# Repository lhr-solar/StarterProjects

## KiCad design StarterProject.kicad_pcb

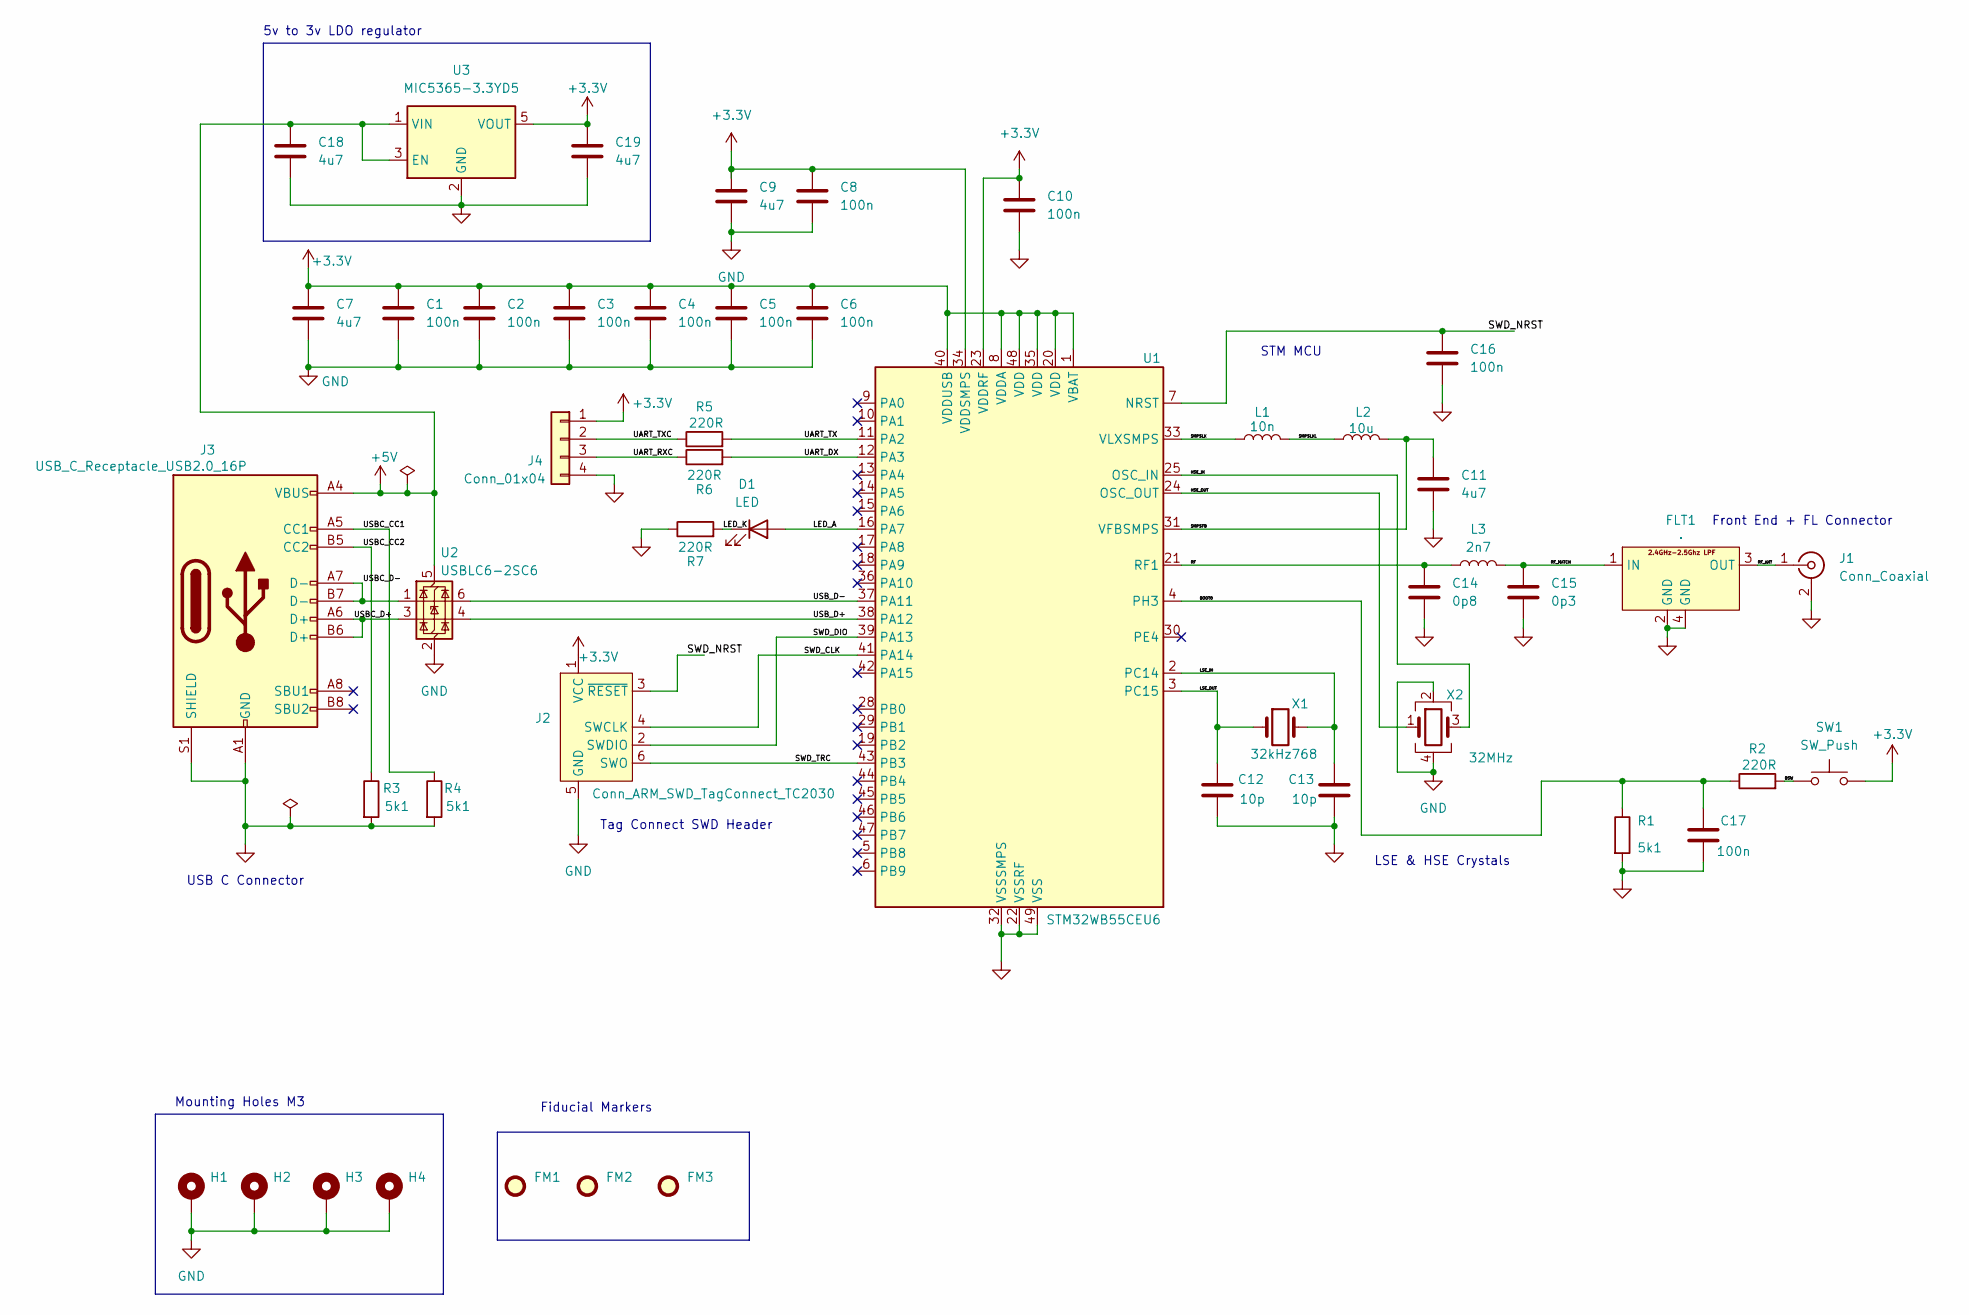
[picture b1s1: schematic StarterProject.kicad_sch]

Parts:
C1, C2, C3, C4, C5, C6, C8, C10, C16, C17: 100n; C_0402_1005Metric
C7, C9, C11, C18, C19: 4u7; C_0603_1608Metric
C12, C13: 10p; C_0402_1005Metric
C14: 0p8; C_0402_1005Metric
C15: 0p3; C_0402_1005Metric
D1: LED; LED_0402_1005Metric; Part # 150040RS73240
FLT1: DLF162500LT-5028A1; Untitled; Part # DLF162500LT-5028A1
FM1, FM2, FM3: Fiducial; Fiducial_1mm_Mask2mm
H1, H2, H3, H4: MountingHole_Pad; MountingHole_2.2mm_M2_Pad_Via
J1: Conn_Coaxial; U.FL_Hirose_U.FL-R-SMT-1_Vertical
J2: Conn_ARM_SWD_TagConnect_TC2030; Tag-Connect_TC2030-IDC-FP_2x03_P1.27mm_Vertical
J3: USB_C_Receptacle_USB2.0_16P; USB_C_Receptacle_GCT_USB4105-xx-A_16P_TopMnt_Horizontal; Part # USB4105-GF-A
J4: Conn_01x04; Molex_PicoBlade_53048-0410_1x04_P1.25mm_Horizontal; Part # 53048-0410
L1: 10n; L_0402_1005Metric; Part # LQG15HN10NJ02D
L2: 10u; L_0805_2012Metric; Part # LQM21FN100M70L
L3: 2n7; L_0402_1005Metric; Part # LQG15HS2N7S02D
R1, R3, R4: 5k1; R_0402_1005Metric; Part # RC0402FR-075K1L
R2, R5, R6, R7: 220R; R_0402_1005Metric; Part # RC0402FR-0722RL
SW1: SW_Push; SW_SPST_CK_RS282G05A3; Part # RS-282G05A3-SM RT
U1: STM32WB55CEU6; QFN-48-1EP_7x7mm_P0.5mm_EP5.6x5.6mm; Part # STM32WB55CEU6
U2: USBLC6-2SC6; SOT-23-6; Part # USBLC6-2SC6
U3: MIC5365-3.3YD5; TSOT-23-5; Part # MIC5365-3.3YD5-TR
X1: 32kHz768; Crystal_SMD_2012-2Pin_2.0x1.2mm; Part # NX2012SA-32.768K-STD-MUB-1
X2: 32MHz; Crystal_SMD_2016-4Pin_2.0x1.6mm; Part # NX2016SA-32M-EXS00A-CS06465

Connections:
+3.3V: C1.1, C2.1, C3.1, C4.1, C5.1, C6.1, C7.1, C8.1, C9.1, C10.1, C19.1, J2.1 (VCC), J4.1, SW1.2, U1.1 (VBAT), U1.8 (VDDA), U1.20 (VDD), U1.23 (VDDRF), U1.34 (VDDSMPS), U1.35 (VDD), U1.40 (VDDUSB), U1.48 (VDD), U3.5 (VOUT)
+5V: C18.1, J3.A4 (VBUS), J3.A9 (VBUS), J3.B4 (VBUS), J3.B9 (VBUS), U2.5 (VBUS), U3.1 (VIN), U3.3 (EN)
/BOOT0: C17.1, R1.1, R2.1, U1.4 (PH3)
/BSW: R2.2, SW1.1
/HSE_IN: U1.25 (OSC_IN), X2.3
/HSE_OUT: U1.24 (OSC_OUT), X2.1
/LED_A: D1.2 (A), U1.16 (PA7)
/LED_K: D1.1 (K), R7.2
/LSE_IN: C13.1, U1.2 (PC14), X1.2
/LSE_OUT: C12.1, U1.3 (PC15), X1.1
/RF: C14.1, L3.1, U1.21 (RF1)
/RF_ANT: FLT1.3 (OUT), J1.1 (In)
/RF_MATCH: C15.1, FLT1.1 (IN), L3.2
/SMPSFB: C11.1, L2.2, U1.31 (VFBSMPS)
/SMPSLX: L1.1, U1.33 (VLXSMPS)
/SMPSLXL: L1.2, L2.1
/SWD_CLK: J2.4 (SWCLK), U1.41 (PA14)
/SWD_DIO: J2.2 (SWDIO), U1.39 (PA13)
/SWD_NRST: C16.1, J2.3 (~RESET), U1.7 (NRST)
/SWD_TRC: J2.6 (SWO), U1.43 (PB3)
/UART_DX: R6.2, U1.12 (PA3)
/UART_RXC: J4.3, R6.1
/UART_TX: R5.2, U1.11 (PA2)
/UART_TXC: J4.2, R5.1
/USBC_CC1: J3.A5 (CC1), R4.1
/USBC_CC2: J3.B5 (CC2), R3.1
/USBC_D+: J3.A6 (D+), J3.B6 (D+), U2.3 (I/O2)
/USBC_D-: J3.A7 (D-), J3.B7 (D-), U2.1 (I/O1)
/USB_D+: U1.38 (PA12), U2.4 (I/O2)
/USB_D-: U1.37 (PA11), U2.6 (I/O1)
GND: C1.2, C2.2, C3.2, C4.2, C5.2, C6.2, C7.2, C8.2, C9.2, C10.2, C11.2, C12.2, C13.2, C14.2, C15.2, C16.2, C17.2, C18.2, C19.2, FLT1.2 (GND), FLT1.4 (GND), H1.1, H2.1, H3.1, H4.1, J1.2 (Ext), J2.5 (GND), J3.A1 (GND), J3.A12 (GND), J3.B1 (GND), J3.B12 (GND), J3.S1 (SHIELD), J4.4, R1.2, R3.2, R4.2, R7.1, U1.22 (VSSRF), U1.32 (VSSSMPS), U1.49 (VSS), U2.2 (GND), U3.2 (GND), X2.2, X2.4

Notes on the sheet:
STM MCU
Tag Connect SWD Header
Mounting Holes M3
Front End + FL Connector
Fiducial Markers
LSE & HSE Crystals
USB C Connector
5v to 3v LDO regulator

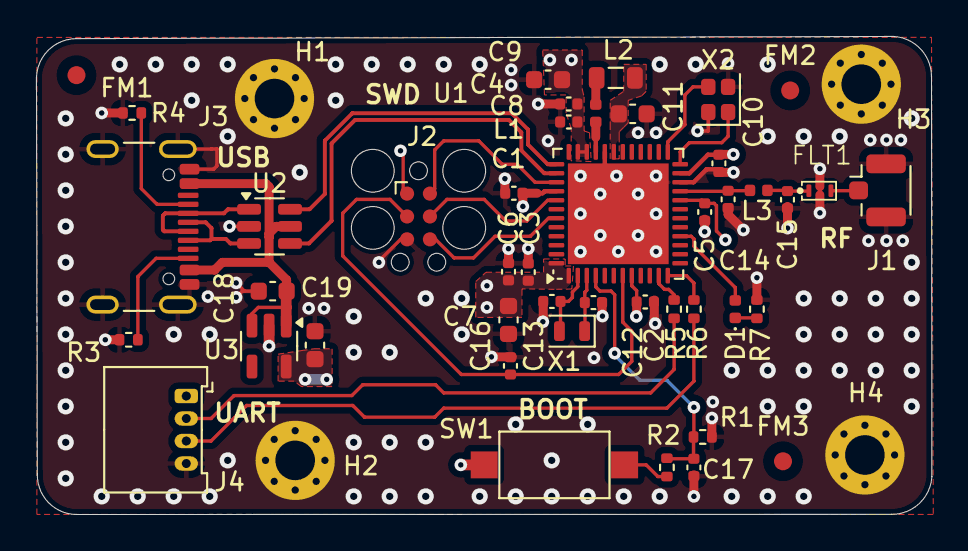
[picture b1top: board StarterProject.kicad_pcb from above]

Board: 4 copper layers, 49.7 x 26.6 mm, 48 parts (0 on the bottom side), 31 nets.

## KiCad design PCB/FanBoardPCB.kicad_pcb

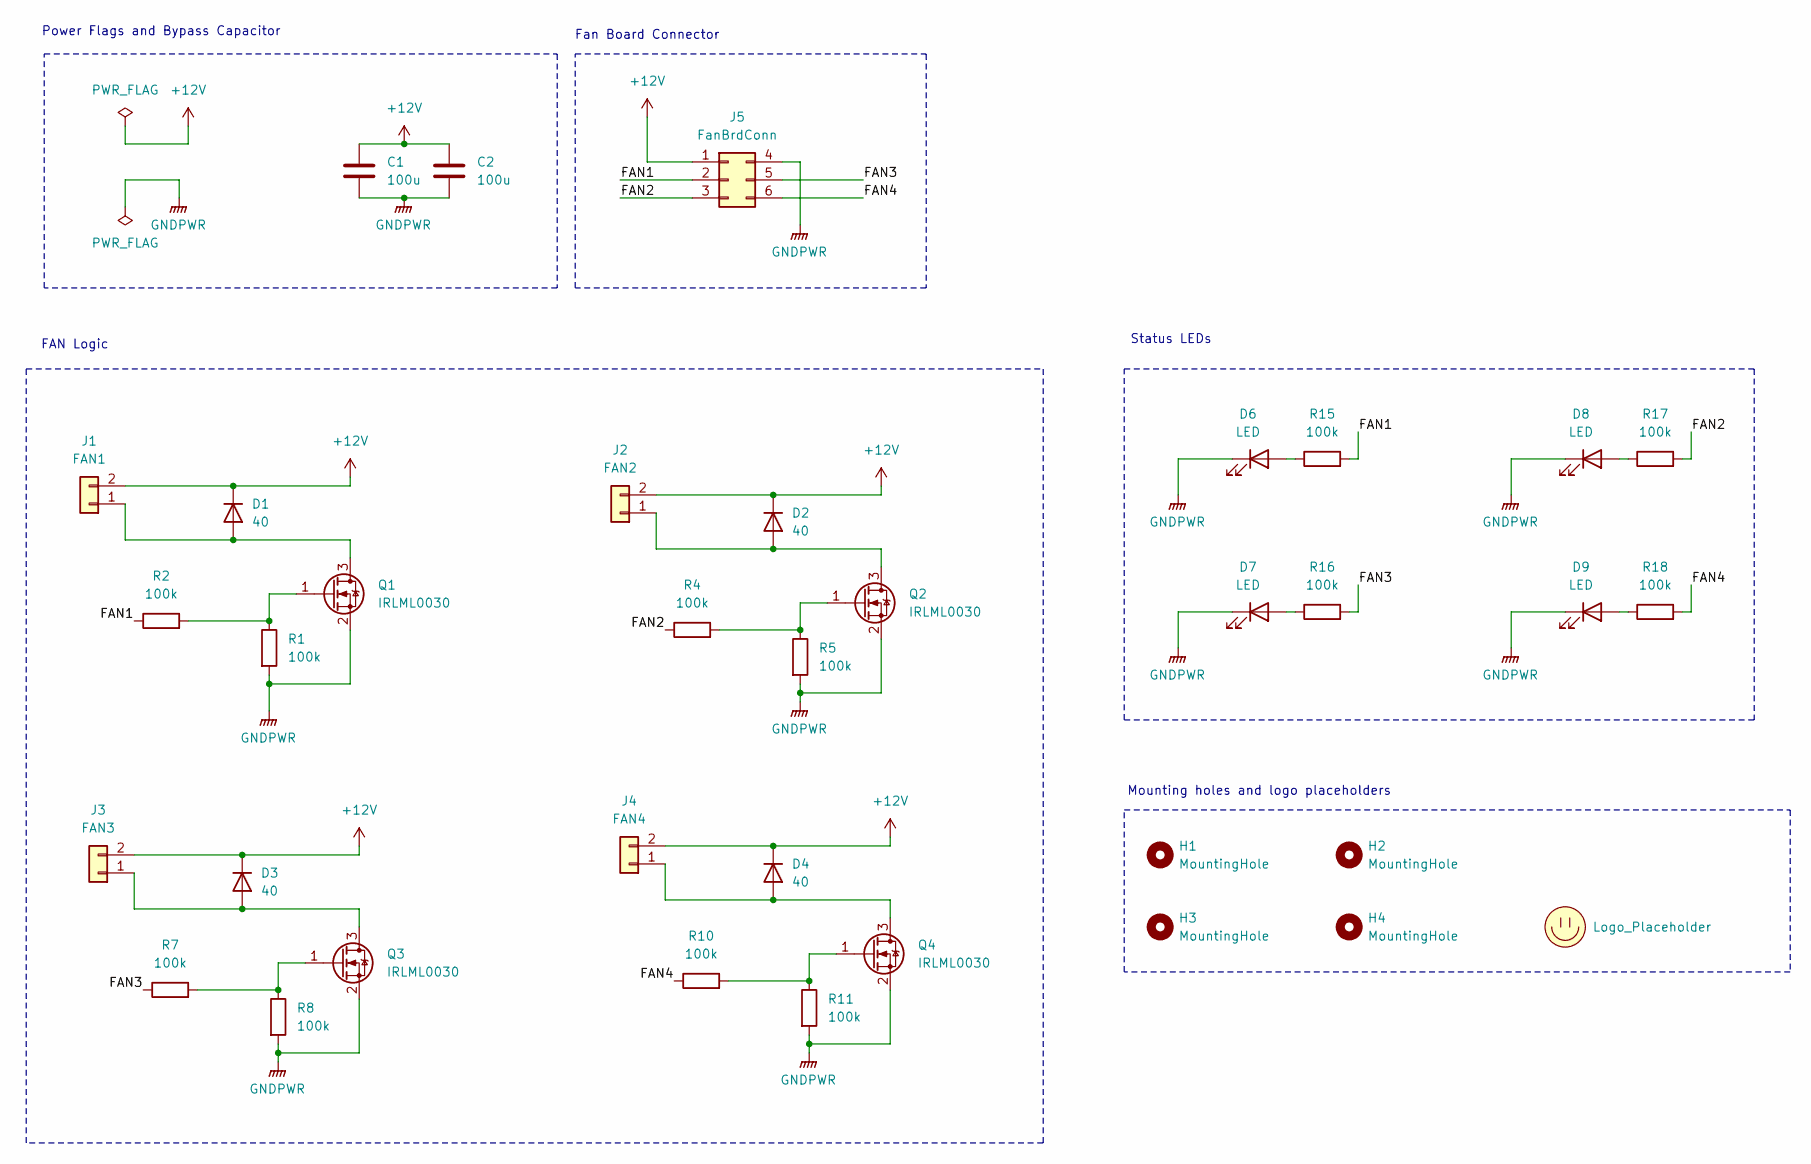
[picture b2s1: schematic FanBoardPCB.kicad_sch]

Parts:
C1, C2: 100u
D1, D2, D3, D4: 40; D_0805_2012Metric
D6, D7, D8, D9: LED; LED_0805_2012Metric
H1, H2, H3, H4: MountingHole; MountingHole_3mm
J1: FAN1; Molex_MicroFit3.0_1x2xP3.00mm_PolarizingPeg_Vertical
J2: FAN2; Molex_MicroFit3.0_1x2xP3.00mm_PolarizingPeg_Vertical
J3: FAN3; Molex_MicroFit3.0_1x2xP3.00mm_PolarizingPeg_Vertical
J4: FAN4; Molex_MicroFit3.0_1x2xP3.00mm_PolarizingPeg_Vertical
J5: FanBrdConn; Molex_Micro-Fit_3.0_43045-0612_2x03_P3.00mm_Vertical
LOGO1: Logo_Placeholder; UTSVT_Logo_Symbol
Q1, Q2, Q3, Q4: IRLML0030; SOT-23
R1, R2, R4, R5, R7, R8, R10, R11, R15, R16, R17, R18: 100k; R_0805_2012Metric

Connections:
+12V: C1.1, C2.1, D1.1 (K), D2.1 (K), D3.1 (K), D4.1 (K), J1.2, J2.2, J3.2, J4.2, J5.1
/FAN1: J5.2, R2.1, R15.2
/FAN2: J5.3, R4.1, R17.2
/FAN3: J5.5, R7.1, R16.2
/FAN4: J5.6, R10.1, R18.2
GNDPWR: C1.2, C2.2, D6.1 (K), D7.1 (K), D8.1 (K), D9.1 (K), J5.4, Q1.2 (S), Q2.2 (S), Q3.2 (S), Q4.2 (S), R1.2, R5.2, R8.2, R11.2
unnamed: D1.2 (A), J1.1, Q1.3 (D)
unnamed: D2.2 (A), J2.1, Q2.3 (D)
unnamed: D3.2 (A), J3.1, Q3.3 (D)
unnamed: D4.2 (A), J4.1, Q4.3 (D)
unnamed: D6.2 (A), R15.1
unnamed: D7.2 (A), R16.1
unnamed: D8.2 (A), R17.1
unnamed: D9.2 (A), R18.1
unnamed: Q1.1 (G), R1.1, R2.2
unnamed: Q2.1 (G), R4.2, R5.1
unnamed: Q3.1 (G), R7.2, R8.1
unnamed: Q4.1 (G), R10.2, R11.1

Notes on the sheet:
Status LEDs
FAN Logic
Power Flags and Bypass Capacitor
Fan Board Connector
Mounting holes and logo placeholders

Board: 2 copper layers, 36 parts (0 on the bottom side), 18 nets, no tracks yet.

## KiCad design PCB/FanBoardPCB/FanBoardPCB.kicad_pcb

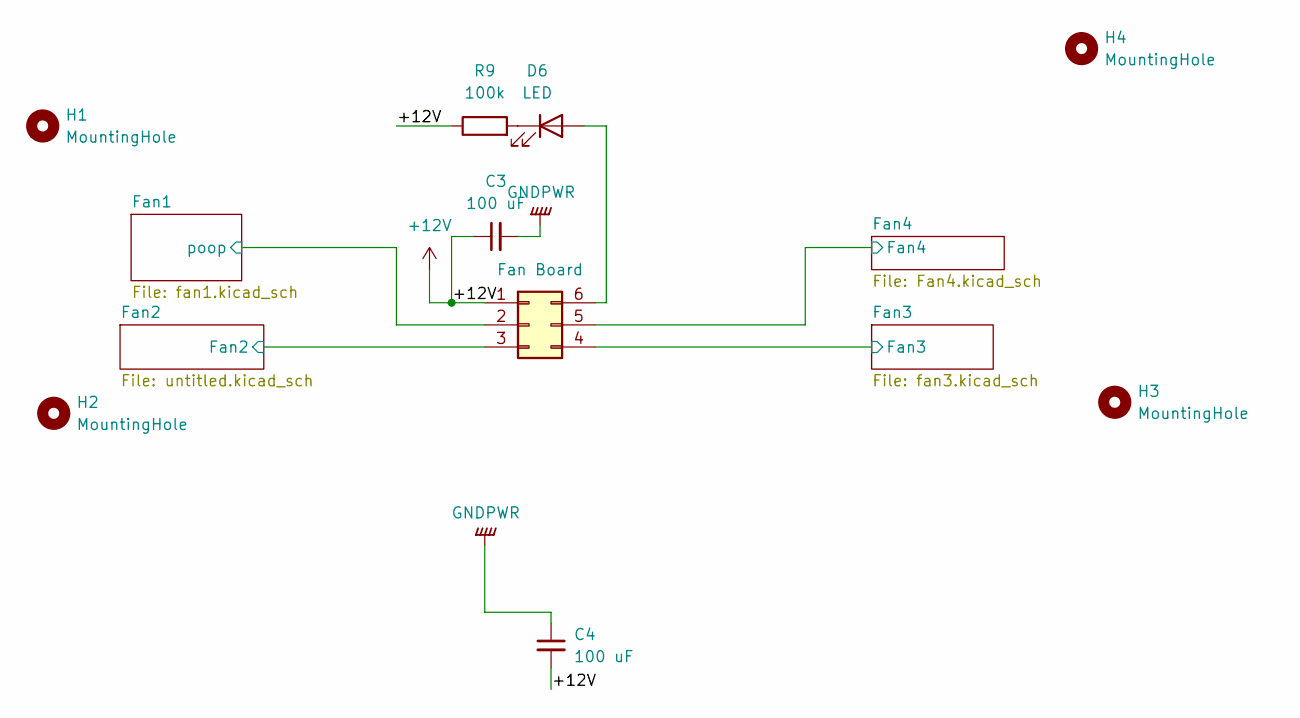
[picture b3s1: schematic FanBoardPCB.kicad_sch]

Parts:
C3, C4: 100 uF; C_0805_2012Metric
D6: LED; LED_0805_2012Metric
H1, H2, H3, H4: MountingHole; MountingHole_3mm
J5: Fan Board; Molex_Micro-Fit_3.0_43045-0612_2x03_P3.00mm_Vertical
R9: 100k; R_0805_2012Metric

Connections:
+12V: C3.1, C4.2, J5.1, R9.1; also elsewhere on the board
/Fan1/poop: J5.2; also elsewhere on the board
/Fan2/Fan2: J5.3; also elsewhere on the board
/Fan3/Fan3: J5.4; also elsewhere on the board
/Fan4/Fan4: J5.5; also elsewhere on the board
GNDPWR: C3.2, C4.1
unnamed: D6.2 (A), J5.6
unnamed: D6.1 (K), R9.2

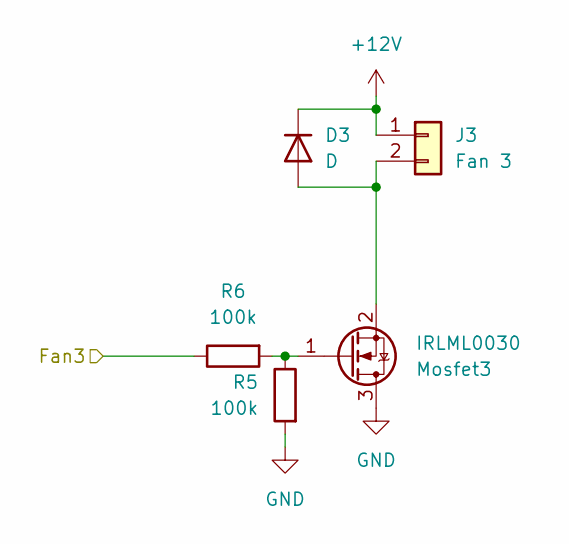
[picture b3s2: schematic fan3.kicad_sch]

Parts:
D3: D; D_0805_2012Metric
J3: Fan 3; Molex_MicroFit3.0_1x2xP3.00mm_PolarizingPeg_Vertical
Mosfet3: IRLML0030; SOT-23
R5, R6: 100k; R_0805_2012Metric

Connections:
+12V: D3.1 (K), J3.1; also elsewhere on the board
/Fan3/Fan3: R6.1; also elsewhere on the board
GND: Mosfet3.3 (D), R5.2; also elsewhere on the board
unnamed: D3.2 (A), J3.2, Mosfet3.2 (S)
unnamed: Mosfet3.1 (G), R5.1, R6.2

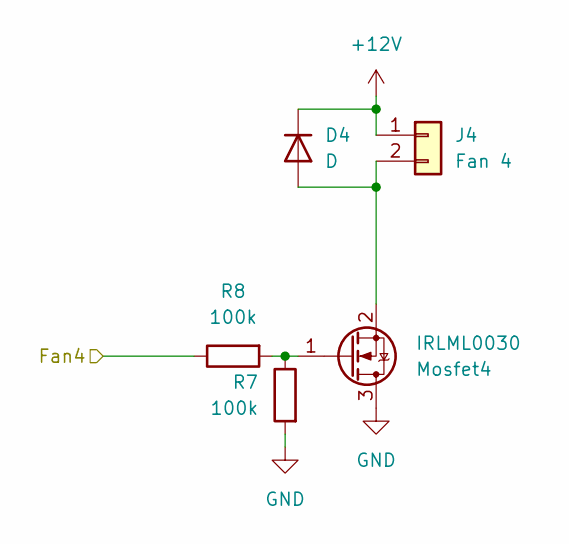
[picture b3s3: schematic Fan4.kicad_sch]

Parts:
D4: D; D_0805_2012Metric
J4: Fan 4; Molex_MicroFit3.0_1x2xP3.00mm_PolarizingPeg_Vertical
Mosfet4: IRLML0030; SOT-23
R7, R8: 100k; R_0805_2012Metric

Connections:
+12V: D4.1 (K), J4.1; also elsewhere on the board
/Fan4/Fan4: R8.1; also elsewhere on the board
GND: Mosfet4.3 (D), R7.2; also elsewhere on the board
unnamed: D4.2 (A), J4.2, Mosfet4.2 (S)
unnamed: Mosfet4.1 (G), R7.1, R8.2

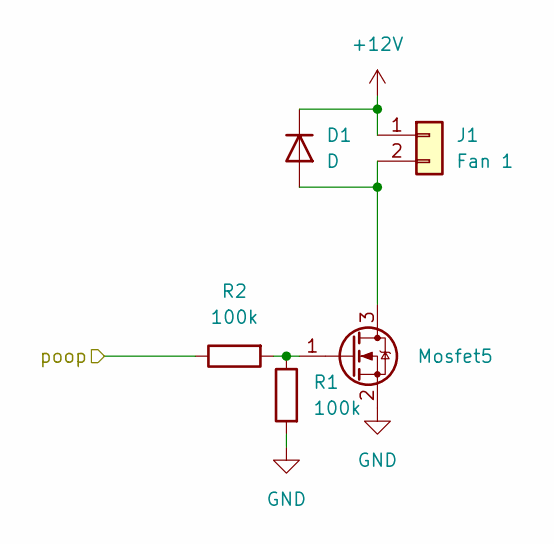
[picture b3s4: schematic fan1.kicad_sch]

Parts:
D1: D; D_0805_2012Metric
J1: Fan 1; Molex_MicroFit3.0_1x2xP3.00mm_PolarizingPeg_Vertical
Mosfet5: IRLML0030; SOT-23
R1, R2: 100k; R_0805_2012Metric

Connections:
+12V: D1.1 (K), J1.1; also elsewhere on the board
/Fan1/poop: R2.1; also elsewhere on the board
GND: Mosfet5.2 (S), R1.2; also elsewhere on the board
unnamed: D1.2 (A), J1.2, Mosfet5.3 (D)
unnamed: Mosfet5.1 (G), R1.1, R2.2

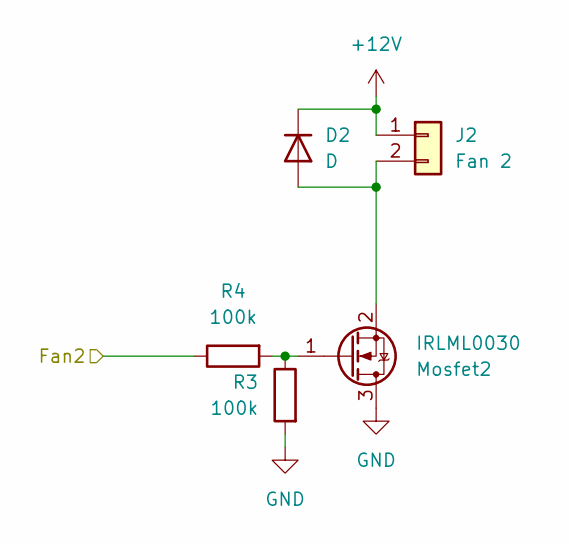
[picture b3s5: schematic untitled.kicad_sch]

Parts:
D2: D; D_0805_2012Metric
J2: Fan 2; Molex_MicroFit3.0_1x2xP3.00mm_PolarizingPeg_Vertical
Mosfet2: IRLML0030; SOT-23
R3, R4: 100k; R_0805_2012Metric

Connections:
+12V: D2.1 (K), J2.1; also elsewhere on the board
/Fan2/Fan2: R4.1; also elsewhere on the board
GND: Mosfet2.3 (D), R3.2; also elsewhere on the board
unnamed: D2.2 (A), J2.2, Mosfet2.2 (S)
unnamed: Mosfet2.1 (G), R3.1, R4.2

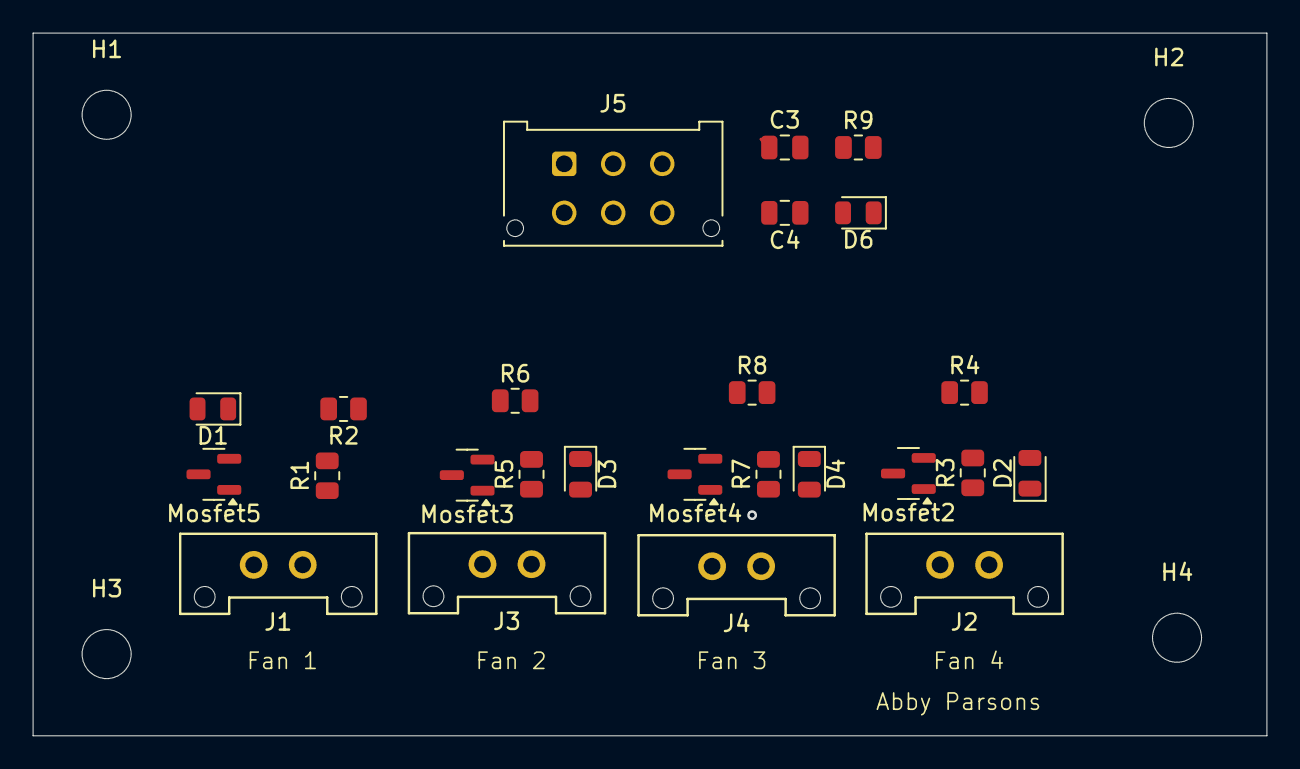
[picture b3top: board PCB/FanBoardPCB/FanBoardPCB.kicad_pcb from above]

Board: 2 copper layers, 75.5 x 43.0 mm, 29 parts (0 on the bottom side), 17 nets.

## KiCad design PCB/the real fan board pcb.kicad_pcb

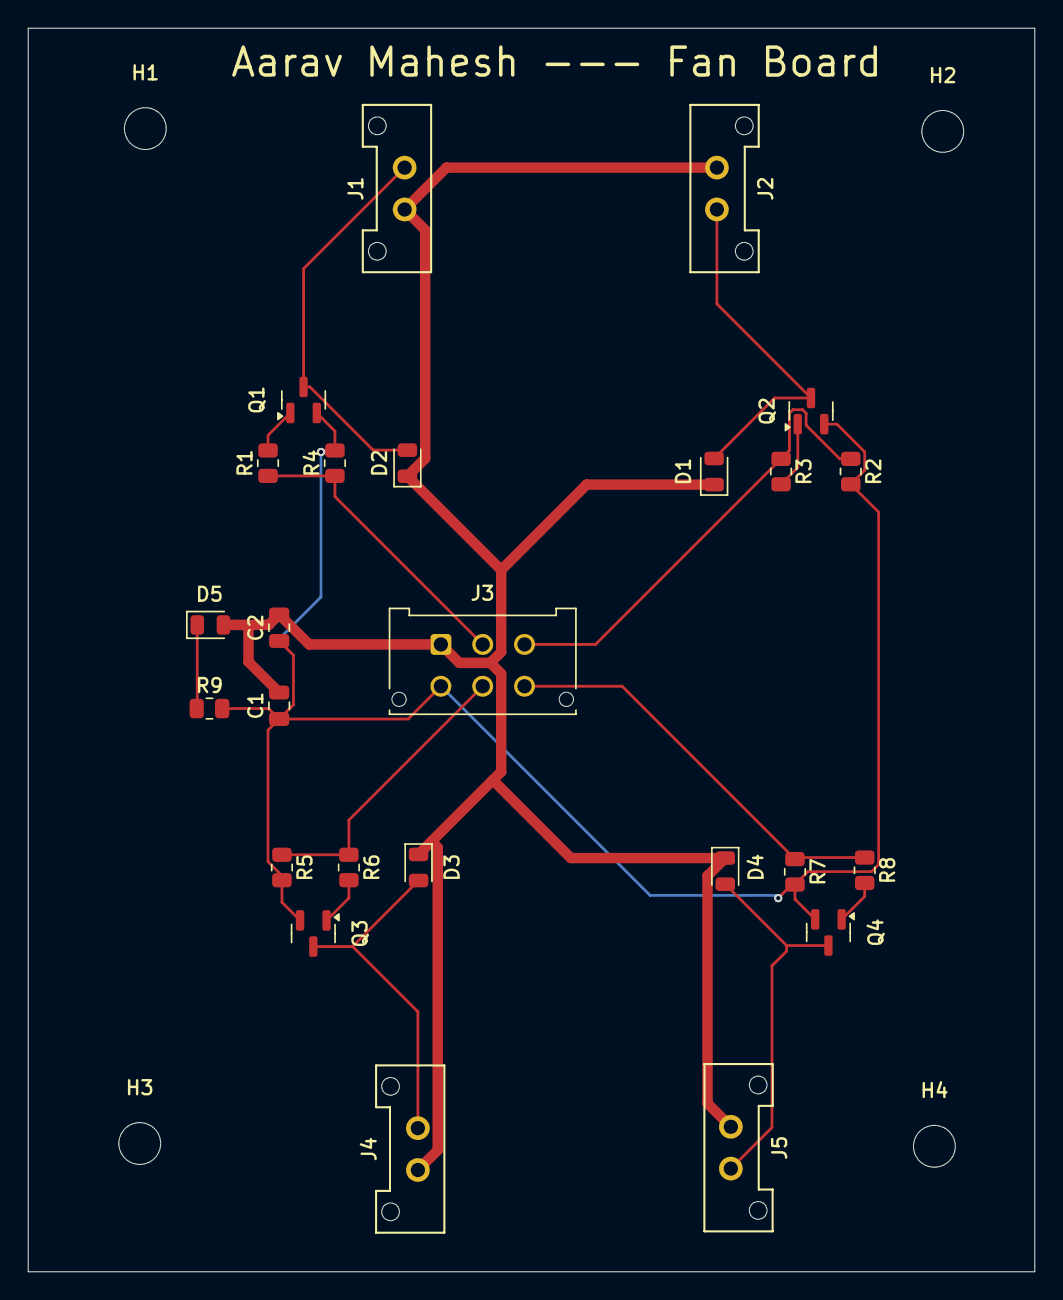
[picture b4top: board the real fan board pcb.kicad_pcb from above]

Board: 2 copper layers, 72.2 x 89.2 mm, 29 parts (0 on the bottom side), 15 nets.

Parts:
C1, C2: 100uF; C_0805_2012Metric
D1, D2, D3, D4: D; D_0805_2012Metric
D5: LED; LED_0805_2012Metric
H1, H2, H3, H4: MountingHole; MountingHole_3mm
J1: FAN1; Molex_MicroFit3.0_1x2xP3.00mm_PolarizingPeg_Vertical
J2: FAN2; Molex_MicroFit3.0_1x2xP3.00mm_PolarizingPeg_Vertical
J3: Conn_02x03_Top_Bottom; Molex_Micro-Fit_3.0_43045-0612_2x03_P3.00mm_Vertical
J4: FAN3; Molex_MicroFit3.0_1x2xP3.00mm_PolarizingPeg_Vertical
J5: FAN4; Molex_MicroFit3.0_1x2xP3.00mm_PolarizingPeg_Vertical
Q1, Q2, Q3, Q4: IRLML0030; SOT-23
R1, R2, R3, R4, R5, R6, R7, R8: 100k; R_0805_2012Metric
R9: 10k; R_0805_2012Metric

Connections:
+12V: C1.2, C2.2, D1.1 (K), D2.1 (K), D3.1 (K), D4.1 (K), D5.2 (A), J1.1, J2.1, J3.1, J4.1, J5.1
/FAN1: J3.2, R1.1, R4.1
/FAN2: J3.3, R2.1, R3.1
/FAN3: J3.5, R5.1, R6.1
/FAN4: J3.6, R7.1, R8.1
GNDPWR: C1.1, C2.1, J3.4, Q1.2 (S), Q2.2 (S), Q3.2 (S), Q4.2 (S), R2.2, R4.2, R5.2, R7.2, R9.2
unnamed: D1.2 (A), J2.2, Q2.3 (D)
unnamed: D2.2 (A), J1.2, Q1.3 (D)
unnamed: D3.2 (A), J4.2, Q3.3 (D)
unnamed: D4.2 (A), J5.2, Q4.3 (D)
unnamed: D5.1 (K), R9.1
unnamed: Q1.1 (G), R1.2
unnamed: Q2.1 (G), R3.2
unnamed: Q3.1 (G), R6.2
unnamed: Q4.1 (G), R8.2

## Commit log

2020-07-24 BPS starter project
2020-08-14 Initial setup
2020-08-14 Reads CSV and prints if row has both columns
2020-08-14 added .o and .exe files to gitignore
2020-08-14 Delay function to delay by one second each time; Call to CAN writing function
2020-08-14 Function written to open file, write necessary message, and close
2020-08-14 Created makefile
2020-08-14 changed delay to use milliseconds as parameter
2020-08-14 Fixes header file parameter type issue
2020-08-14 Fixed make issue
2020-08-14 formatted test print
2020-08-15 Fixed clock delay to use clock_per_seconds; cleaned up while loop
2020-08-15 switched to Uint16_type for memory reasons
2020-08-15 Fixed gitignore to not track CAN.csv
2020-08-15 Untracked CAN.csv properly
2020-08-24 gitignore update
2020-08-24 Fixed int casting issue for delay function
2020-08-24 Changed macro type
2020-08-29 Styled Code per styling guidelines
2020-09-05 almostDone
2020-09-05 fixed spacing
2020-09-05 Almot done except Python
2020-09-05 python almsot done
2020-09-05 fixes
2020-09-05 Finished2.0
2020-09-12 Updates README
2020-10-01 Starter project code, only modified the main file.
2021-04-03 Did Steps 1-4
2021-04-24 finished with starter project
2021-08-28 Nathaniel's Start Project
2021-09-04 created can send function, header file, and main loop call
2021-09-04 got makefile working and finished step 5 (printing csv with python)
2021-09-04 Working.
2021-09-10 Adds DataAcq starter project
2021-09-11 Update Makefile
2021-10-02 scrapes bookstore data and stores in csv file
2021-10-02 reads cleaned data into pandas dataframe
2021-10-02 includes only books with rating of three stars or higher
2021-10-02 plots pandas data as scatter plot
2021-10-02 scrapes, cleans, and plots data
2021-10-02 does not include pkg-resources
2022-02-12 finished the starter project.
2022-02-12 First completion
2022-02-26 Byrn starter project
2022-02-26 This is the final and only of the starter project
2022-08-11 set up basic uCOS-III simulator functionality and documented setup procedure
2022-08-11 fixed rtprio script to actually add current user to realtime group
2022-08-12 fixed makefile, created basic file structure with all functions and comments
2022-08-12 updated readme with instructions on branching/pull request
2022-08-14 Various changes to streamline design, fix issues
2022-08-20 Apply suggestions from code review
2022-08-20 reorganized file structure, allowed for switching between tests with the makefile
2022-08-20 more descriptive comments for TCBs and Stacks
    explicitly said how many seconds to wait in Mailman.c to avoid race condition
2022-08-21 added pointers as parameters to Customer1_checkout and Customer2_checkout
2022-08-22 Fixed swapped Mail/Cafe headers
2022-08-22 Implemented mailman
2022-08-22 implemented recipient
2022-08-22 Completed first half of starter
2022-08-22 Implemented customer 1
2022-08-22 Implemented customer 2
2022-08-22 Finished cafe portion
2022-08-22 made some requested changes
2022-08-27 Last changes
2022-08-27 first
2022-08-27 2022-23 New Starter Project (#16)
    * set up basic uCOS-III simulator functionality and documented setup procedure
    * fixed rtprio script to actually add current user to realtime group
    * fixed makefile, created basic file structure with all functions and comments
    * updated readme
    * updated readme with instructions on branching/pull request
    * Various changes to streamline design, fix issues
2022-09-10 gitignore to ignore dsstore
2022-09-10 gitignore2.0
2022-09-10 starter project scrape, clean
2022-09-10 gitignore __pycache__
2022-09-10 final wrap up
2022-09-17 initial commit
    Update clean, scrape, visualize, and main
2022-09-17 All changes for Cafe without running Cafe to check if it works. Because I haven't figured out Make yet.
2022-09-24 finished up clean
2022-09-24 First attempt at completing the Mail challenge. I think enough things should be filled out for it to work (hopefully), although I haven't added error checking yet.
2022-09-24 finished cleaning
2022-09-24 finished visualization and final clean up
2022-09-24 Added a "watermark stack limit" of 128 (half of stack size) to Tasks.h Attempted to complete the test file for Mail, though error checking still not finished Will now try to actually fun files.
2022-09-24 cafe now working, running correctly
2022-09-24 A version of the code that actually compiles! Includes a finished test file for Mail. Error checking is still not finished- should be made a function instead of repeated printfs Random number snprint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
2022-09-24 Finished Stater Project!
2022-09-24 Mail compiles and seems to work correctly! Still need to clean it up and do better error checking.
2022-10-01 Editing my code for Ishan's requests...But not changing barely any formatting because Sidharth said so.
2022-10-01 Starter Project Finish -Gage :)
2022-10-01 Attempted to fill out Cafe files. Doesn't compile due to unused variable.
2022-10-01 Working version of Cafe! Removed unused err
2022-10-01 deleted comments
2022-10-01 FInished Mailman
2022-10-01 Finished starter project! Or at least it works and isn't messy.
2022-10-02 Added JSDOC @param comments, moved mutex protection so resource isn't blocked longer than necessary, changed name to item_name
2022-10-08 Finished Starter Project
2022-10-08 prints item cost
2022-10-08 used identifiers and adding check for errors
2022-10-08 Fixed print statement
2022-10-15 Final project
2022-10-22 Added OS_ERR and CPU_TS variable declarations for functions where mutex pends/posts were added and removed CPU_TS declaration where unused so that Cafe actually compiles.
2022-10-22 Day 5:AM - FINISHED
2023-09-23 Complete first code of mail/semaphor files
2023-09-23 Correct random number range to 1-9999
2023-09-23 made changes to the depositletter() function
2023-09-24 Finish Cafe files
2023-09-24 Moved cafe revenue print to checkout function
2023-09-24 Fix order of mail semaphor reading
2023-09-24 Add full error checking to Test_Cafe
2023-09-29 Simplify mailbox message posting
2023-09-29 Moved error handling around
2023-09-30 added error checks on all tasks, wrote readMail() function on Recipient, and initialized tasks in Tests
2023-09-30 mailman and recipient functionality added
2023-09-30 corrected logic errors and increased readability
2023-09-30 update test for mailman, testing error handling
2023-09-30 Mailbox - error @ Task_Mailman
2023-09-30 Error @ Customer1_checkout. Seems like the same error from mailman proj
2023-09-30 mail test corrected some more and added micrium
2023-09-30 Removed print error statement, was printing out garbage value
2023-09-30 finished mailman test
2023-09-30 finished cafe and added better error handling
2023-09-30 fixed the formatting on printing out the mailbox contents, fixed error checks, middle of testing
2023-09-30 better delay handling
2023-09-30 need to implement task init for part 1
2023-09-30 wrote functions from customer 1 and customer 2, wrote test_cafe, will start testing after
2023-09-30 part 1 finished, not tested
2023-09-30 fixed the ticks and error definitions on a function from customer 2
2023-10-07 Created code for mailman and recipient tasks, initialized in Test_Mail.c, not yet tested
2023-10-07 compiled code, fixed errors where variables were declared twice, test is not printing
2023-10-07 took semaphore post command out of if statement
2023-10-07 added an include statement to recipient
2023-10-07 working code
2023-10-07 created Customer1_checkout
2023-10-07 finished testing and editing test files
2023-10-07 completed task_customer_1
2023-10-07 completed customer2_checkout and created mutex in test_cafe
2023-10-07 finished task_customer_2, placed most commands in task_customer_2 and task_customer_1 in loop
2023-10-07 initialized customer 1 and 2
2023-10-07 deleted unneeded line
2023-10-14 finished
2024-09-28 soup
2024-09-28 add basic symbols
2024-09-29 add initial schematic
2024-09-29 add mounting holes
2024-09-29 yippeeeeee
2024-09-30 add status LED and footprints
2024-09-30 create initial layout
2024-10-01 Initial Version of board and schematic.
2024-10-02 Modified PCB layout to reduce trace/via amounts.
2024-10-02 Added untracked files
2024-10-02 initial pcb commit
2024-10-02 starter project i guess
2024-10-02 updated traces
2024-10-02 Updated footprints/layout for better connections.
2024-10-02 better layout and traces
2024-10-02 generate gerbers
2024-10-02 Merge remote-tracking branch 'origin' into diya
    Merging to get new fan board project from master.
2024-10-03 add net labels
2024-10-03 cleanup PCB
2024-10-04 jacob guidry starter project
2024-10-04 Added Schematic
    Not sure if its right tho :0
2024-10-04 Updated schematic/PCB
2024-10-04 Initial commit, laid out schematic, feelin roasted toasted
2024-10-04 Layout #3 for PCB.
2024-10-04 Fixed Sch
2024-10-04 modified pcb latout
2024-10-04 Flipped the MOLEX for clip to face inward.
2024-10-04 Added pwr flags to remove ERC errors
2024-10-05 Silly little compact board :)
2024-10-05 Rotated Connectors, Thicker Traces, and Two Ground Planes
2024-10-05 fixed trace width ??
2024-10-05 Fixed schematic and silkscreen updates
2024-10-05 drc is happy
2024-10-05 added a guy on it
2024-10-05 fix resistors and simplify layout
2024-10-05 finalize board
2024-10-05 sorted out git stuff
2024-10-05 deleted extra pcb duplicates
2024-10-05 deleted random file
2024-10-05 Started on PCB
2024-10-05 Updated PCB
2024-10-05 Updated PCB again :)
2024-10-05 added top 12V and bottom GND planes
2024-10-05 Finished I think :)
2024-10-05 Done, I think:)
2024-10-08 yippeee! schem fixed probably
2024-10-08 ishan is annoying (joke)
2024-10-08 adjusted led down to 5mA, still kinda a lot admittedly, 15mW for the led and 60mW for the whole circuit
2024-10-08 gndpwr moment
2024-10-09 layout (it probably sucks)
2024-10-09 moved some traces
2024-10-09 something
2024-10-09 fixed
2024-10-09 fan labels
2024-10-10 clean up schematic more
2024-10-10 testpoints
2024-10-10 initial push scematic first draft
2024-10-12 addressed comments, started PCB layout but disregard
2024-10-12 This is what I changed
2024-10-15 finished PCB
2024-10-17 cleaned schematic, addressed comments
2024-10-19 Jacob_ActivePrecharge_Attempt2
2024-10-25 started schematic
2024-10-25 schematic done??
2024-10-25 r pt 2
2024-10-30 fixed board schematic a bit
2024-11-02 Supplemental Monitoring Board
2025-02-15 working on Mail.c
2025-03-01 commented out Mail.c
2025-03-28 working on recipient
2025-03-28 readmail written
2025-03-28 recipient done
2025-03-28 minor changes to mail and recipient
2025-03-28 more minor changes
2025-04-01 recipient
2025-04-04 recipient changes
2025-04-04 rough draft
2025-04-04 Close to done
2025-04-05 erros fixed
2025-04-12 Test Cafe
2025-04-12 Mail Test
2025-04-12 testing
2025-04-12 os issues
2025-09-04 like 60% done?
2025-09-13 finished first draft
2025-09-13 address review comments
2025-09-30 Fix formatting error on StarterProj
2025-09-30 changes to main.c
2025-10-03 move code into txtask
2025-10-04 led and send works
